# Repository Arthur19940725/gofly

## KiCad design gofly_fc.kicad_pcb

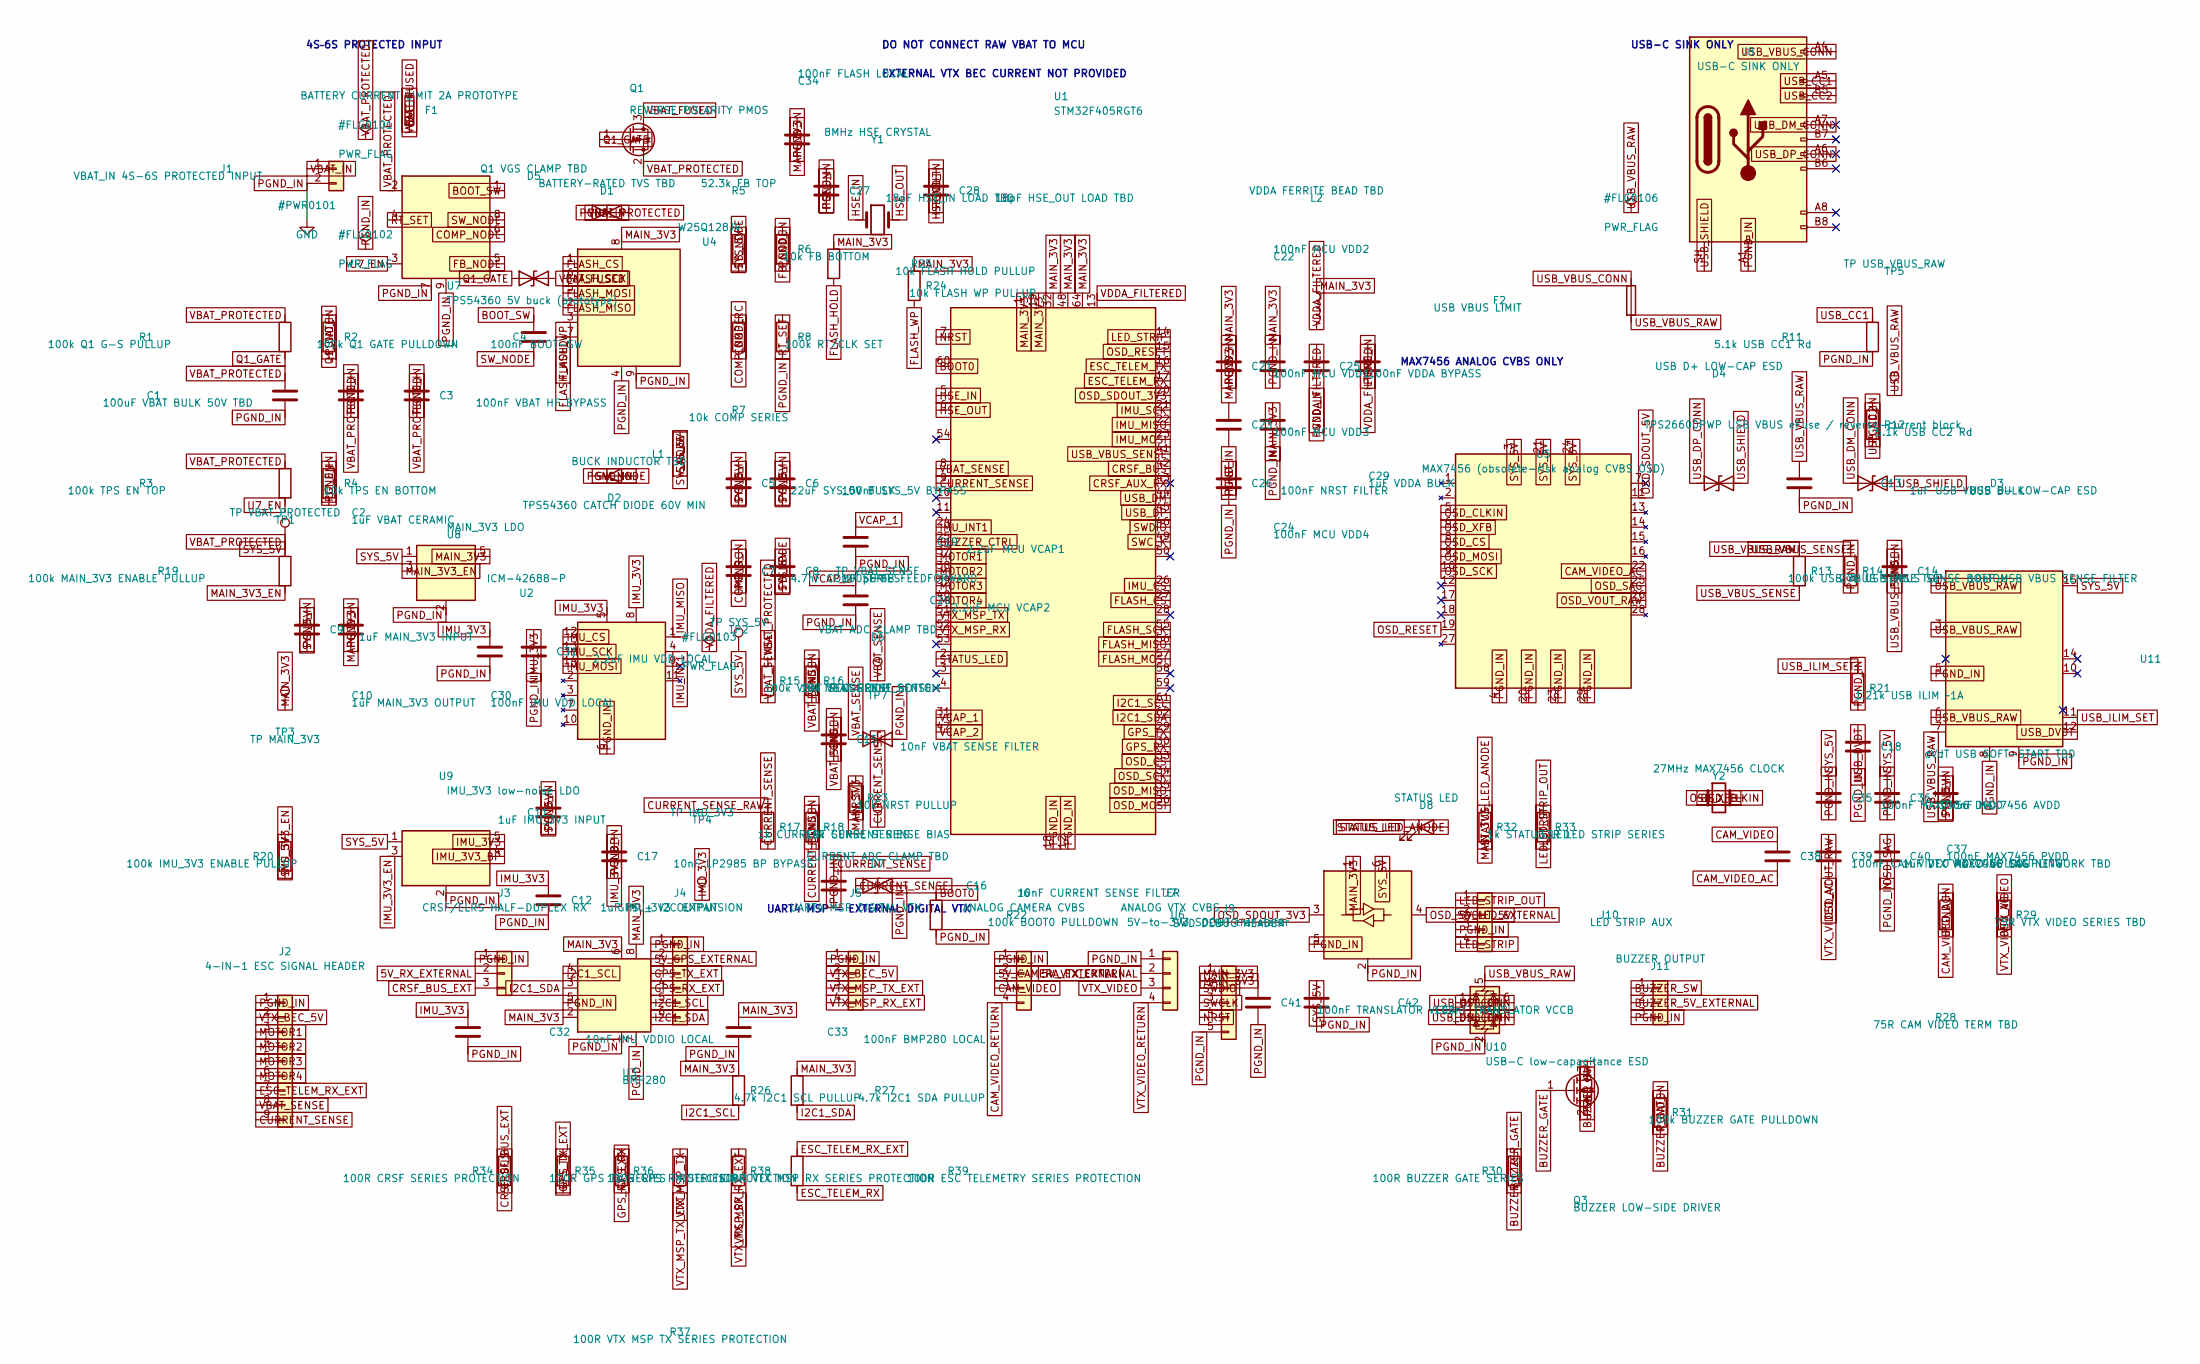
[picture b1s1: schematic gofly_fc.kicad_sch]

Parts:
C1: 100uF VBAT BULK 50V TBD; C_1210_3225Metric
C2: 1uF VBAT CERAMIC; C_0805_2012Metric
C3: 100nF VBAT HF BYPASS; C_0603_1608Metric
C4: 100nF BOOT-SW; C_0603_1608Metric
C5: 22uF SYS_5V BULK; C_1210_3225Metric
C6: 100nF SYS_5V BYPASS; C_0603_1608Metric
C7: 4.7nF COMP SERIES; C_0603_1608Metric
C8: 100pF FB FEEDFORWARD; C_0603_1608Metric
C9: 1uF MAIN_3V3 INPUT; C_0603_1608Metric
C10: 1uF MAIN_3V3 OUTPUT; C_0603_1608Metric
C11: 1uF IMU_3V3 INPUT; C_0603_1608Metric
C12: 1uF IMU_3V3 OUTPUT; C_0603_1608Metric
C13: 1uF USB VBUS BULK; C_0805_2012Metric
C14: 10nF USB VBUS SENSE FILTER; C_0603_1608Metric
C15: 10nF VBAT SENSE FILTER; C_0603_1608Metric
C16: 10nF CURRENT SENSE FILTER; C_0603_1608Metric
C17: 10nF LP2985 BP BYPASS; C_0603_1608Metric
C18: dVdT USB SOFT-START TBD; C_0603_1608Metric
C19: 2.2uF MCU VCAP1; C_0805_2012Metric
C20: 2.2uF MCU VCAP2; C_0805_2012Metric
C21: 100nF MCU VDD1; C_0603_1608Metric
C22: 100nF MCU VDD2; C_0603_1608Metric
C23: 100nF MCU VDD3; C_0603_1608Metric
C24: 100nF MCU VDD4; C_0603_1608Metric
C25: 100nF VDDA BYPASS; C_0603_1608Metric
C26: 100nF NRST FILTER; C_0603_1608Metric
C27: 18pF HSE_IN LOAD TBD; C_0603_1608Metric
C28: 18pF HSE_OUT LOAD TBD; C_0603_1608Metric
C29: 1uF VDDA BULK; C_0805_2012Metric
C30: 100nF IMU VDD LOCAL; C_0603_1608Metric
C31: 2.2uF IMU VDD LOCAL; C_0805_2012Metric
C32: 10nF IMU VDDIO LOCAL; C_0603_1608Metric
C33: 100nF BMP280 LOCAL; C_0603_1608Metric
C34: 100nF FLASH LOCAL; C_0603_1608Metric
C35: 100nF MAX7456 DVDD; C_0603_1608Metric
C36: 100nF MAX7456 AVDD; C_0603_1608Metric
C37: 100nF MAX7456 PVDD; C_0603_1608Metric
C38: 100nF CAM VIDEO AC COUPLING; C_0603_1608Metric
C39: 1uF VTX VIDEO AC COUPLING; C_0603_1608Metric
C40: MAX7456 SAG NETWORK TBD; C_0603_1608Metric
C41: 100nF TRANSLATOR VCCA; C_0603_1608Metric
C42: 100nF TRANSLATOR VCCB; C_0603_1608Metric
D1: BATTERY-RATED TVS TBD; D_SMA
D2: TPS54360 CATCH DIODE 60V MIN; D_SMA
D3: USB D- LOW-CAP ESD; D_SOD-523
D4: USB D+ LOW-CAP ESD; D_SOD-523
D5: Q1 VGS CLAMP TBD; D_0603_1608Metric
D6: VBAT ADC CLAMP TBD; D_0603_1608Metric
D7: CURRENT ADC CLAMP TBD; D_0603_1608Metric
D8: STATUS LED; LED_0603_1608Metric
F1: BATTERY CURRENT LIMIT 2A PROTOTYPE; Fuse_1206_3216Metric
F2: USB VBUS LIMIT; Fuse_1206_3216Metric
J1: VBAT_IN 4S-6S PROTECTED INPUT; PinHeader_1x02_P2.54mm_Vertical
J2: 4-IN-1 ESC SIGNAL HEADER; PinHeader_1x09_P2.54mm_Vertical
J3: CRSF/ELRS HALF-DUPLEX RX; PinHeader_1x03_P2.54mm_Vertical
J4: GPS + I2C EXPANSION; PinHeader_1x06_P2.54mm_Vertical
J5: UART4 MSP DIGITAL VTX; PinHeader_1x04_P2.54mm_Vertical
J6: ANALOG CAMERA CVBS; PinHeader_1x04_P2.54mm_Vertical
J7: ANALOG VTX CVBS; PinHeader_1x04_P2.54mm_Vertical
J8: USB-C SINK ONLY; USB_C_Receptacle_GCT_USB4105-xx-A_16P_TopMnt_Horizontal
J9: SWD DEBUG HEADER; PinHeader_1x05_P2.54mm_Vertical
J10: LED STRIP AUX; PinHeader_1x04_P2.54mm_Vertical
J11: BUZZER OUTPUT; PinHeader_1x03_P2.54mm_Vertical
L1: BUCK INDUCTOR TBD; L_1210_3225Metric
L2: VDDA FERRITE BEAD TBD; L_0603_1608Metric
Q1: REVERSE POLARITY PMOS; SOT-23
Q3: BUZZER LOW-SIDE DRIVER; SOT-23
R1: 100k Q1 G-S PULLUP; R_0603_1608Metric
R2: 100k Q1 GATE PULLDOWN; R_0603_1608Metric
R3: 100k TPS EN TOP; R_0603_1608Metric
R4: 10k TPS EN BOTTOM; R_0603_1608Metric
R5: 52.3k FB TOP; R_0603_1608Metric
R6: 10k FB BOTTOM; R_0603_1608Metric
R7: 10k COMP SERIES; R_0603_1608Metric
R8: 100k RT/CLK SET; R_0603_1608Metric
R11: 5.1k USB CC1 Rd; R_0603_1608Metric
R12: 5.1k USB CC2 Rd; R_0603_1608Metric
R13: 100k USB VBUS SENSE TOP; R_0603_1608Metric
R14: 27k USB VBUS SENSE BOTTOM; R_0603_1608Metric
R15: 100k VBAT SENSE TOP; R_0603_1608Metric
R16: 18k VBAT SENSE BOTTOM; R_0603_1608Metric
R17: 1k CURRENT SENSE SERIES; R_0603_1608Metric
R18: 10k CURRENT SENSE BIAS; R_0603_1608Metric
R19: 100k MAIN_3V3 ENABLE PULLUP; R_0603_1608Metric
R20: 100k IMU_3V3 ENABLE PULLUP; R_0603_1608Metric
R21: 1.21k USB ILIM ~1A; R_0603_1608Metric
R22: 100k BOOT0 PULLDOWN; R_0603_1608Metric
R23: 10k NRST PULLUP; R_0603_1608Metric
R24: 10k FLASH WP PULLUP; R_0603_1608Metric
R25: 10k FLASH HOLD PULLUP; R_0603_1608Metric
R26: 4.7k I2C1 SCL PULLUP; R_0603_1608Metric
R27: 4.7k I2C1 SDA PULLUP; R_0603_1608Metric
R28: 75R CAM VIDEO TERM TBD; R_0603_1608Metric
R29: 75R VTX VIDEO SERIES TBD; R_0603_1608Metric
R30: 100R BUZZER GATE SERIES; R_0603_1608Metric
R31: 100k BUZZER GATE PULLDOWN; R_0603_1608Metric
R32: 1k STATUS LED; R_0603_1608Metric
R33: 33R LED STRIP SERIES; R_0603_1608Metric
R34: 100R CRSF SERIES PROTECTION; R_0603_1608Metric
R35: 100R GPS TX SERIES PROTECTION; R_0603_1608Metric
R36: 100R GPS RX SERIES PROTECTION; R_0603_1608Metric
R37: 100R VTX MSP TX SERIES PROTECTION; R_0603_1608Metric
R38: 100R VTX MSP RX SERIES PROTECTION; R_0603_1608Metric
R39: 100R ESC TELEMETRY SERIES PROTECTION; R_0603_1608Metric
TP1: TP VBAT_PROTECTED; TestPoint_Plated_Hole_D2.0mm
TP2: TP SYS_5V; TestPoint_Plated_Hole_D2.0mm
TP3: TP MAIN_3V3; TestPoint_Plated_Hole_D2.0mm
TP4: TP IMU_3V3; TestPoint_Plated_Hole_D2.0mm
TP5: TP USB_VBUS_RAW; TestPoint_Plated_Hole_D2.0mm
TP6: TP VBAT_SENSE; TestPoint_Plated_Hole_D2.0mm
TP7: TP CURRENT_SENSE; TestPoint_Plated_Hole_D2.0mm
U1: STM32F405RGT6; LQFP-64_10x10mm_P0.5mm
U2: ICM-42688-P; Bosch_LGA-14_3x2.5mm_P0.5mm
U3: BMP280; Bosch_LGA-8_2.5x2.5mm_P0.65mm_ClockwisePinNumbering
U4: W25Q128JV; WSON-8-1EP_8x6mm_P1.27mm_EP3.4x4.3mm
U5: MAX7456 (obsolete-risk analog CVBS OSD); TSSOP-28-1EP_4.4x9.7mm_P0.65mm_EP2.74x4.75mm
U6: 5V-to-3V3 SDOUT translator; SOT-23-6
U7: TPS54360 5V buck (prototype); TI_SO-PowerPAD-8_ThermalVias
U8: MAIN_3V3 LDO; SOT-23-5
U9: IMU_3V3 low-noise LDO; SOT-23-5
U10: USB-C low-capacitance ESD; SOT-23-6
U11: TPS26600PWP USB VBUS eFuse / reverse-current block; HTSSOP-16-1EP_4.4x5mm_P0.65mm_EP3.4x5mm_Mask2.66x2.46mm_The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
Y1: 8MHz HSE CRYSTAL; Crystal_SMD_3225-4Pin_3.2x2.5mm
Y2: 27MHz MAX7456 CLOCK; Crystal_SMD_3225-4Pin_3.2x2.5mm

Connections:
5V_CAMERA_EXTERNAL: J6.2
5V_GPS_EXTERNAL: J4.2
5V_LED_EXTERNAL: J10.2
5V_RX_EXTERNAL: J3.2
5V_VTX_EXTERNAL: J7.2
BOOT0: R22.1, U1.60 (BOOT0)
BOOT_SW: C4.1, U7.1 (BOOT)
BUZZER_5V_EXTERNAL: J11.2
BUZZER_CTRL: R30.1, U1.25 (PC5)
BUZZER_GATE: Q3.1 (G), R30.2, R31.1
BUZZER_SW: J11.1, Q3.3 (D)
CAM_VIDEO: C38.1, J6.3
CAM_VIDEO_AC: C38.2, R28.1, U5.22 (VIN)
CAM_VIDEO_RETURN: J6.4
COMP_NODE: R7.1, U7.6 (COMP)
COMP_RC: C7.1, R7.2
CRSF_AUX_RX: U1.43 (PA10)
CRSF_BUS: R34.1, U1.42 (PA9)
CRSF_BUS_EXT: J3.3, R34.2
CURRENT_SENSE: C16.1, D7.1 (A1), J2.9, R17.2, R18.1, TP7.1, U1.9 (PC1)
CURRENT_SENSE_RAW: R17.1
ESC_TELEM_RX: R39.2, U1.17 (PA3)
ESC_TELEM_RX_EXT: J2.7, R39.1
ESC_TELEM_TX: U1.16 (PA2)
FB_NODE: C8.2, R5.2, R6.1, U7.5 (FB)
FLASH_CS: U1.27 (PB1), U4.1 (~CS)
FLASH_HOLD: R25.2, U4.7 (~HOLD/~RESET/IO_{3})
FLASH_MISO: U1.56 (PB4), U4.2 (DO/IO_{1})
FLASH_MOSI: U1.57 (PB5), U4.5 (DI/IO_{0})
FLASH_SCK: U1.55 (PB3), U4.6 (CLK)
FLASH_WP: R24.2, U4.3 (~WP/IO_{2})
GPS_RX: R36.2, U1.30 (PB11)
GPS_RX_EXT: J4.4, R36.1
GPS_TX: R35.1, U1.29 (PB10)
GPS_TX_EXT: J4.3, R35.2
HSE_IN: C27.1, U1.5 (PH0), Y1.1
HSE_OUT: C28.1, U1.6 (PH1), Y1.2
I2C1_SCL: J4.5, R26.2, U1.61 (PB8), U3.4 (SCK)
I2C1_SDA: J4.6, R27.2, U1.62 (PB9), U3.3 (SDI)
IMU_3V3: C12.1, C30.1, C31.1, C32.1, TP4.1, U2.5 (VDDIO), U2.8 (VDD), U9.5 (VOUT)
IMU_3V3_BP: C17.1, U9.4 (BP)
IMU_3V3_EN: R20.2, U9.3 (ON/~OFF)
IMU_CS: U1.26 (PB0), U2.12 (AP_CS)
IMU_INT1: U1.24 (PC4), U2.4 (INT1 / INT)
IMU_MISO: U1.22 (PA6), U2.1 (AP_SDO / AP_AD0)
IMU_MOSI: U1.23 (PA7), U2.14 (AP_SDA / AP_SDIO / AP_SDI)
IMU_SCK: U1.21 (PA5), U2.13 (AP_SCL / AP_SCLK)
LED_STRIP: J10.4, R33.1, U1.14 (PA0)
LED_STRIP_OUT: J10.1, R33.2
MAIN_3V3: C10.1, C21.1, C22.1, C23.1, C24.1, C33.1, C34.1, C41.1, J9.1, L2.1, R23.1, R24.1, R25.1, R26.1, R27.1, R32.1, TP3.1, U1.1 (VBAT), U1.19 (VDD), U1.32 (VDD), U1.48 (VDD), U1.64 (VDD), U3.2 (CSB), U3.6 (VDDIO), U3.8 (VDD), U4.8 (VCC), U6.1 (VCCA), U8.5 (VOUT)
MAIN_3V3_EN: R19.2, U8.3 (EN)
MOTOR1: J2.3, U1.37 (PC6)
MOTOR2: J2.4, U1.38 (PC7)
MOTOR3: J2.5, U1.39 (PC8)
MOTOR4: J2.6, U1.40 (PC9)
NRST: C26.1, J9.4, R23.2, U1.7 (NRST)
OSD_CLKIN: U5.5 (CLKIN), Y2.1
OSD_CS: U1.33 (PB12), U5.8 (CS)
OSD_MISO: U1.35 (PB14)
OSD_MOSI: U1.36 (PB15), U5.9 (SDIN)
OSD_RESET: U1.15 (PA1), U5.19 (RESET)
OSD_SAG: C40.1, U5.25 (SAG)
OSD_SCK: U1.34 (PB13), U5.10 (SCLK)
OSD_SDOUT_3V3: U1.20 (PA4), U6.3 (A)
OSD_SDOUT_5V: U5.11 (SDOUT), U6.4 (B)
OSD_VOUT_RAW: C39.1, U5.26 (VOUT)
OSD_XFB: U5.6 (XFB), Y2.2
PGND_IN: C1.2, C2.2, C3.2, C5.2, C6.2, C7.2, C9.2, C10.2, C11.2, C12.2, C13.2, C14.2, C15.2, C16.2, C17.2, C18.2, C19.2, C20.2, C21.2, C22.2, C23.2, C24.2, C25.2, C26.2, C27.2, C28.2, C29.2, C30.2, C31.2, C32.2, C33.2, C34.2, C35.2, C36.2, C37.2, C40.2, C41.2, C42.2, D1.2 (A2), D2.2 (A), D6.2 (A2), D7.2 (A2), J1.2, J2.1, J3.1, J4.1, J5.1, J6.1, J7.1, J8.A1 (GND), J8.A12 (GND), J8.B1 (GND), J8.B12 (GND), J9.5, J10.3, J11.3, Q3.2 (S), R2.2, R4.2, R6.2, R8.2, R11.2, R12.2, R14.2, R16.2, R18.2, R21.2, R22.2, R28.2, R31.2, U1.12 (VSSA), U1.18 (VSS), U1.63 (VSS), U2.6 (GND), U3.1 (GND), U3.5 (SDO), U3.7 (GND), U4.4 (GND), U4.9 (EP), U5.4 (DGND), U5.20 (AGND), U5.23 (PGND), U5.29 (EP), U6.2 (GND), U6.5 (DIR), U7.7 (GND), U7.9 (GNDPAD), U8.2 (GND), U9.2 (GND), U10.2 (GND), U11.5 (OVP), U11.8 (RTN), U11.9 (GND), U11.17 (RTN)
Q1_GATE: D5.1 (A1), Q1.1 (G), R1.2, R2.1
RT_SET: R8.1, U7.4 (RT/CLK)
STATUS_LED: D8.1 (K), U1.2 (PC13)
STATUS_LED_ANODE: D8.2 (A), R32.2
SWCLK: J9.3, U1.49 (PA14)
SWDIO: J9.2, U1.46 (PA13)
SW_NODE: C4.2, D2.1 (K), L1.1, U7.8 (SW)
SYS_5V: C5.1, C6.1, C8.1, C9.1, C11.1, C35.1, C36.1, C37.1, C42.1, L1.2, R5.1, R19.1, R20.1, TP2.1, U5.3 (DVDD), U5.21 (AVDD), U5.24 (PVDD), U6.6 (VCCB), U8.1 (VIN), U9.1 (VIN), U11.15 (OUT), U11.16 (OUT)
U7_EN: R3.2, R4.1, U7.3 (EN)
USB_CC1: J8.A5 (CC1), R11.1
USB_CC2: J8.B5 (CC2), R12.1
USB_DM: U1.44 (PA11), U10.3 (I/O2)
USB_DM_CONN: D3.1 (A1), J8.A7 (D-), U10.4 (I/O2)
USB_DP: U1.45 (PA12), U10.1 (I/O1)
USB_DP_CONN: D4.1 (A1), J8.A6 (D+), U10.6 (I/O1)
USB_DVDT: C18.1, U11.12 (dVdT)
USB_ILIM_SET: R21.1, U11.11 (ILIM)
USB_SHIELD: D3.2 (A2), D4.2 (A2), J8.SH (SHIELD)
USB_VBUS_CONN: F2.1, J8.A4 (VBUS), J8.A9 (VBUS), J8.B4 (VBUS), J8.B9 (VBUS)
USB_VBUS_RAW: C13.1, F2.2, R13.1, TP5.1, U10.5 (VBUS), U11.1 (IN), U11.2 (IN), U11.3 (UVLO), U11.6 (MODE), U11.7 (~SHDN)
USB_VBUS_SENSE: C14.1, R13.2, R14.1, U1.41 (PA8)
VBAT_FUSED: D5.2 (A2), F1.2, Q1.3 (D)
VBAT_IN: F1.1, J1.1
VBAT_PROTECTED: C1.1, C2.1, C3.1, D1.1 (A1), Q1.2 (S), R1.1, R3.1, R15.1, TP1.1, U7.2 (VIN)
VBAT_SENSE: C15.1, D6.1 (A1), J2.8, R15.2, R16.1, TP6.1, U1.8 (PC0)
VCAP_1: C19.1, U1.31 (VCAP_1)
VCAP_2: C20.1, U1.47 (VCAP_2)
VDDA_FILTERED: C25.1, C29.1, L2.2, U1.13 (VDDA)
VTX_BEC_5V: J2.2, J5.2
VTX_MSP_RX: R38.2, U1.52 (PC11)
VTX_MSP_RX_EXT: J5.4, R38.1
VTX_MSP_TX: R37.1, U1.51 (PC10)
VTX_MSP_TX_EXT: J5.3, R37.2
VTX_VIDEO: J7.3, R29.2
VTX_VIDEO_AC: C39.2, R29.1
VTX_VIDEO_RETURN: J7.4

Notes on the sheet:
4S–6S PROTECTED INPUT
USB-C SINK ONLY
MAX7456 ANALOG CVBS ONLY
UART4 MSP — EXTERNAL DIGITAL VTX
DO NOT CONNECT RAW VBAT TO MCU
EXTERNAL VTX BEC CURRENT NOT PROVIDED

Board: 4 copper layers, 128 parts (0 on the bottom side), 92 nets, no tracks yet.

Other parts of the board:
MH1, MH2, MH3, MH4: MountingHole_3.2mm

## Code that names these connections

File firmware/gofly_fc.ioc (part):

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Mcu.Name=STM32F405RGT6
Mcu.Package=LQFP64
Mcu.UserName=STM32F405RGT6
PA0.GPIOParameters=GPIO_Label
PA0.GPIO_Label=LED_STRIP
PA0.Signal=GPIO_Output
PA1.GPIOParameters=GPIO_Label
PA1.GPIO_Label=OSD_RESET
PA1.Signal=GPIO_Output
PA2.Mode=Asynchronous
PA2.Signal=USART2_TX
PA3.Mode=Asynchronous
PA3.Signal=USART2_RX
PA5.Mode=Full_Duplex_Master
PA5.Signal=SPI1_SCK
PA6.Mode=Full_Duplex_Master
PA6.Signal=SPI1_MISO
PA7.Mode=Full_Duplex_Master
PA7.Signal=SPI1_MOSI
PA8.GPIOParameters=GPIO_Label
PA8.GPIO_Label=USB_VBUS_SENSE
PA8.Signal=GPIO_Input
PA9.Mode=Asynchronous
PA9.Signal=USART1_TX
PA10.Mode=Asynchronous
PA10.Signal=USART1_RX
PA11.Mode=Device_Only
PA11.Signal=USB_OTG_FS_DM
PA12.Mode=Device_Only
PA12.Signal=USB_OTG_FS_DP
PA13.Mode=Serial_Wire
PA13.Signal=SYS_SWDIO
PA14.Mode=Serial_Wire
PA14.Signal=SYS_SWCLK
PB0.GPIOParameters=GPIO_Label
PB0.GPIO_Label=IMU_CS
PB0.Signal=GPIO_Output
PB1.GPIOParameters=GPIO_Label
PB1.GPIO_Label=FLASH_CS
PB1.Signal=GPIO_Output
PB3.Mode=Full_Duplex_Master
PB3.Signal=SPI3_SCK
PB4.Mode=Full_Duplex_Master
PB4.Signal=SPI3_MISO
PB5.Mode=Full_Duplex_Master
PB5.Signal=SPI3_MOSI
PB8.Mode=I2C
PB8.Signal=I2C1_SCL
PB9.Mode=I2C
PB9.Signal=I2C1_SDA
PB10.Mode=Asynchronous
PB10.Signal=USART3_TX
PB11.Mode=Asynchronous
PB11.Signal=USART3_RX
PB12.GPIOParameters=GPIO_Label
PB12.GPIO_Label=OSD_CS
PB12.Signal=GPIO_Output
PB13.Mode=Full_Duplex_Master
PB13.Signal=SPI2_SCK
PB14.Mode=Full_Duplex_Master
PB14.Signal=SPI2_MISO
PB15.Mode=Full_Duplex_Master
PB15.Signal=SPI2_MOSI
PC0.Mode=ADC1_IN10
PC0.Signal=ADC1_IN10
PC1.Mode=ADC1_IN11
PC1.Signal=ADC1_IN11
PC4.GPIOParameters=GPIO_Label,GPIO_ModeDefaultEXTI
PC4.GPIO_Label=IMU_INT1
PC4.Signal=GPXTI4
PC5.GPIOParameters=GPIO_Label
PC5.GPIO_Label=BUZZER_CTRL
PC5.Signal=GPIO_Output
PC6.Mode=PWM Generation CH1
PC6.Signal=TIM3_CH1
PC7.Mode=PWM Generation CH2
PC7.Signal=TIM3_CH2
PC8.Mode=PWM Generation CH3
PC8.Signal=TIM3_CH3
PC9.Mode=PWM Generation CH4
PC9.Signal=TIM3_CH4
PC10.Mode=Asynchronous
PC10.Signal=UART4_TX
PC11.Mode=Asynchronous
PC11.Signal=UART4_RX
PC13.GPIOParameters=GPIO_Label
PC13.GPIO_Label=STATUS_LED
PC13.Signal=GPIO_Output
PH0-OSC_IN.Mode=HSE-External-Oscillator
PH0-OSC_IN.Signal=RCC_OSC_IN
PH1-OSC_OUT.Mode=HSE-External-Oscillator
PH1-OSC_OUT.Signal=RCC_OSC_OUT
RCC.HSE_VALUE=8000000
RCC.SYSCLKFreq_VALUE=168000000
RCC.SYSCLKSource=RCC_SYSCLKSOURCE_PLLCLK

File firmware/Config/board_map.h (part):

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#define GOFLY_IMU_CS_PIN 0U
#define GOFLY_IMU_INT1_PORT GOFLY_GPIO_PORT_C
#define GOFLY_IMU_INT1_PIN 4U
#define GOFLY_SIGNAL_NAME_IMU_SCK "IMU_SCK"
#define GOFLY_SIGNAL_NAME_IMU_MISO "IMU_MISO"
#define GOFLY_SIGNAL_NAME_IMU_MOSI "IMU_MOSI"
#define GOFLY_SIGNAL_NAME_IMU_CS "IMU_CS"
#define GOFLY_SIGNAL_NAME_IMU_INT1 "IMU_INT1"

#define GOFLY_FLASH_SPI_INSTANCE 3U
#define GOFLY_FLASH_SPI_NAME "SPI3"
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#define GOFLY_FLASH_MOSI_PIN 5U
#define GOFLY_FLASH_CS_PORT GOFLY_GPIO_PORT_B
#define GOFLY_FLASH_CS_PIN 1U
#define GOFLY_SIGNAL_NAME_FLASH_SCK "FLASH_SCK"
#define GOFLY_SIGNAL_NAME_FLASH_MISO "FLASH_MISO"
#define GOFLY_SIGNAL_NAME_FLASH_MOSI "FLASH_MOSI"
#define GOFLY_SIGNAL_NAME_FLASH_CS "FLASH_CS"

#define GOFLY_OSD_SPI_INSTANCE 2U
#define GOFLY_OSD_SPI_NAME "SPI2"
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#define GOFLY_OSD_CS_PIN 12U
#define GOFLY_OSD_RESET_PORT GOFLY_GPIO_PORT_A
#define GOFLY_OSD_RESET_PIN 1U
#define GOFLY_SIGNAL_NAME_OSD_SCK "OSD_SCK"
#define GOFLY_SIGNAL_NAME_OSD_MISO "OSD_MISO"
#define GOFLY_SIGNAL_NAME_OSD_MOSI "OSD_MOSI"
#define GOFLY_SIGNAL_NAME_OSD_CS "OSD_CS"
#define GOFLY_SIGNAL_NAME_OSD_RESET "OSD_RESET"

#define GOFLY_BARO_I2C_INSTANCE 1U
#define GOFLY_BARO_I2C_NAME "I2C1"
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#define GOFLY_GPS_RX_PORT GOFLY_GPIO_PORT_B
#define GOFLY_GPS_RX_PIN 11U
#define GOFLY_GPS_UART_BAUD 57600UL
#define GOFLY_SIGNAL_NAME_GPS_TX "GPS_TX"
#define GOFLY_SIGNAL_NAME_GPS_RX "GPS_RX"

#define GOFLY_VTX_UART_INSTANCE 4U
#define GOFLY_VTX_UART_NAME "UART4"
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#define GOFLY_VTX_TX_PIN 10U
#define GOFLY_VTX_RX_PORT GOFLY_GPIO_PORT_C
#define GOFLY_VTX_RX_PIN 11U
#define GOFLY_SIGNAL_NAME_VTX_TX "VTX_MSP_TX"
#define GOFLY_SIGNAL_NAME_VTX_RX "VTX_MSP_RX"

#define GOFLY_ESC_UART_INSTANCE 2U
#define GOFLY_ESC_UART_NAME "USART2"
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#define GOFLY_ESC_RX_PORT GOFLY_GPIO_PORT_A
#define GOFLY_ESC_RX_PIN 3U
#define GOFLY_SIGNAL_NAME_ESC_TX "ESC_TELEM_TX"
#define GOFLY_SIGNAL_NAME_ESC_RX "ESC_TELEM_RX"

#define GOFLY_MOTOR_TIMER_INSTANCE 3U
#define GOFLY_MOTOR_TIMER_NAME "TIM3"
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#define GOFLY_BATTERY_ADC_PIN 0U
#define GOFLY_CURRENT_ADC_PORT GOFLY_GPIO_PORT_C
#define GOFLY_CURRENT_ADC_PIN 1U
#define GOFLY_SIGNAL_NAME_BATTERY_ADC "VBAT_SENSE"
#define GOFLY_SIGNAL_NAME_CURRENT_ADC "CURRENT_SENSE"

#define GOFLY_USB_INSTANCE "USB_OTG_FS"
#define GOFLY_USB_DM_PORT GOFLY_GPIO_PORT_A
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#define GOFLY_USB_DP_PIN 12U
#define GOFLY_USB_VBUS_PORT GOFLY_GPIO_PORT_A
#define GOFLY_USB_VBUS_PIN 8U
#define GOFLY_SIGNAL_NAME_USB_DM "USB_DM"
#define GOFLY_SIGNAL_NAME_USB_DP "USB_DP"
#define GOFLY_SIGNAL_NAME_USB_VBUS "USB_VBUS_SENSE"

#define GOFLY_SWDIO_PORT GOFLY_GPIO_PORT_A
#define GOFLY_SWDIO_PIN 13U
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#define GOFLY_TIM6_INSTANCE 6U
#define GOFLY_TIM6_NAME "TIM6"
#define GOFLY_TIM6_TICK_RATE_HZ 1000U
#define GOFLY_SIGNAL_NAME_LED_STRIP "LED_STRIP"
#define GOFLY_SIGNAL_NAME_BUZZER "BUZZER"
#define GOFLY_SIGNAL_NAME_STATUS_LED "STATUS_LED"

#if (GOFLY_IMU_SCK_PORT == GOFLY_GPIO_PORT_E) || \
    (GOFLY_IMU_MISO_PORT == GOFLY_GPIO_PORT_E) || \
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
#if GOFLY_USB_DM_PORT != GOFLY_GPIO_PORT_A || GOFLY_USB_DM_PIN != 11U || \
    GOFLY_USB_DP_PORT != GOFLY_GPIO_PORT_A || GOFLY_USB_DP_PIN != 12U
#error "USB FS must use PA11 USB_DM and PA12 USB_DP"
#endif

#if GOFLY_BATTERY_ADC_PORT != GOFLY_GPIO_PORT_C || \
    GOFLY_BATTERY_ADC_PIN != 0U || \
    GOFLY_CURRENT_ADC_PORT != GOFLY_GPIO_PORT_C || \
    GOFLY_CURRENT_ADC_PIN != 1U
#error "ADC inputs must use PC0 battery sense and PC1 current sense"
#endif

#endif
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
